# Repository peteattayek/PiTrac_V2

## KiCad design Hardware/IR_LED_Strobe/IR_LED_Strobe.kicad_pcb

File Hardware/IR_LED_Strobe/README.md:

# IR LED strobe array

This two-layer emitter board connects to J3 on the [controller](../The_One_Board_To_Rule_Them_All/README.md).
The controller contains the driver; this board carries the LEDs and their series resistors.
Open [IR_LED_Strobe.kicad_pro](IR_LED_Strobe.kicad_pro) to edit it, or read the
[two-sheet schematic PDF](exports/IR_LED_Strobe.pdf). See the [wiring guide, section 5](../../WIRING_DIAGRAM.md#5-irled--irled2-strobe-board-wiring-j3)
for the connector pinout. `VIR-` is the switched return, not ground.

## Current assembly

The PCB has four parallel strings of five LED positions. **Only the two middle rows
are fitted: 10 LEDs, not 20** (owner-confirmed 2026-11-20). The schematic and layout
show the full design, not just the fitted parts.

| Row in PCB editor (top to bottom) | LED references | Current assembly |
|---|---|---|
| 1 | D1–D5 | Empty |
| 2 | D6–D10 | Fitted |
| 3 | D11–D15 | Fitted |
| 4 | D16–D20 | Empty |

## Files

- [PCB layout](IR_LED_Strobe.kicad_pcb) and [root schematic](IR_LED_Strobe.kicad_sch).
  The only child sheet is [IRLED.kicad_sch](IRLED.kicad_sch).
- [VSMA1085250.pretty](VSMA1085250.pretty/) contains the LED footprint recovered from
  the original PCB. The library name matches the layout; the LED specified in the
  schematic is `VSMA1085400x02`.
- [exports/](exports/) contains the schematic PDF and the original [mechanical STEP](exports/IR_LED_Strobe.step).
- [jlcpcb/production_files/](jlcpcb/production_files/) contains the original Gerber ZIP,
  assembly BOM and placement list. Their historical filenames are intentional.
  The BOM and placement list contain R1–R4 only; neither is a list of the fitted LEDs.

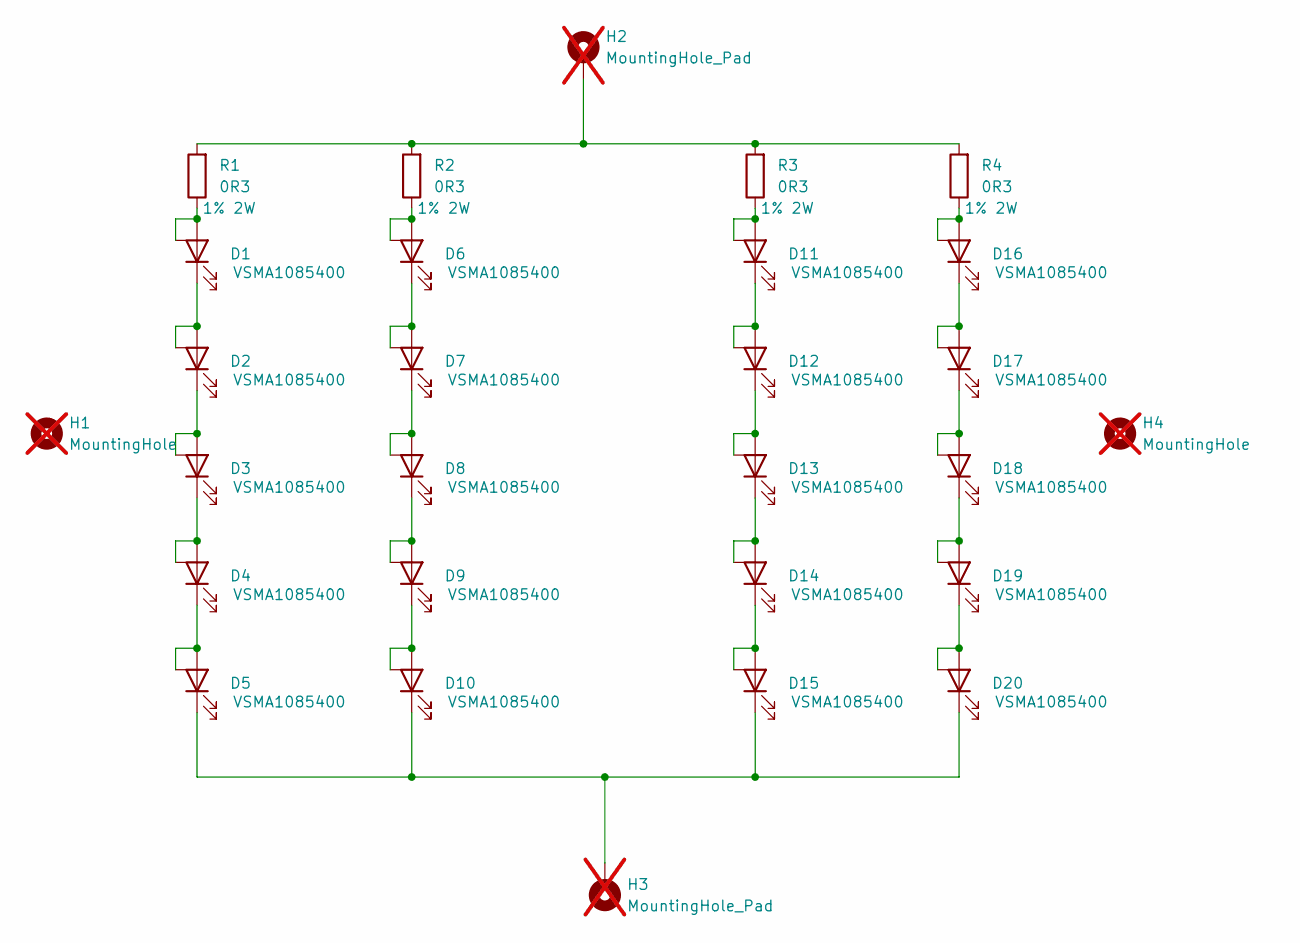
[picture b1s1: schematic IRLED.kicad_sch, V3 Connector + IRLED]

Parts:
D1, D2, D3, D4, D5, D6, D7, D8, D9, D10, D11, D12, D13, D14, D15, D16, D17, D18, D19, D20: VSMA1085400x02; DIODE_VSMA1085250_VIS; Part Number VSMA1085400
H1, H4: MountingHole; MountingHole_3.2mm_M3; not fitted
H2, H3: MountingHole_Pad; MountingHole_2.2mm_M2_Pad; not fitted
R1, R2, R3, R4: 0R3; R_2512_6332Metric; Ratings 1% 2W; Part Number KNP100JR-73-0R1; LCSC C149850

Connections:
unnamed: D1.2 (A), D1.3, R1.1
unnamed: D1.1 (K), D2.2 (A), D2.3
unnamed: D2.1 (K), D3.2 (A), D3.3
unnamed: D3.1 (K), D4.2 (A), D4.3
unnamed: D4.1 (K), D5.2 (A), D5.3
unnamed: D6.2 (A), D6.3, R2.1
unnamed: D6.1 (K), D7.2 (A), D7.3
unnamed: D7.1 (K), D8.2 (A), D8.3
unnamed: D8.1 (K), D9.2 (A), D9.3
unnamed: D9.1 (K), D10.2 (A), D10.3
unnamed 10: D5.1 (K), D10.1 (K), D15.1 (K), D20.1 (K), H3.1; also elsewhere on the board
unnamed: D11.2 (A), D11.3, R3.1
unnamed: D11.1 (K), D12.2 (A), D12.3
unnamed: D12.1 (K), D13.2 (A), D13.3
unnamed: D13.1 (K), D14.2 (A), D14.3
unnamed: D14.1 (K), D15.2 (A), D15.3
unnamed: D16.2 (A), D16.3, R4.1
unnamed: D16.1 (K), D17.2 (A), D17.3
unnamed: D17.1 (K), D18.2 (A), D18.3
unnamed: D18.1 (K), D19.2 (A), D19.3
unnamed: D19.1 (K), D20.2 (A), D20.3
unnamed 21: H2.1, R1.2, R2.2, R3.2, R4.2; also elsewhere on the board

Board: 2 copper layers, 28 parts (0 on the bottom side), 22 nets, no tracks yet.

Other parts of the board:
VIR+: MountingHole_Pad; MountingHole_2.2mm_M2_Pad
VIR-: MountingHole_Pad; MountingHole_2.2mm_M2_Pad

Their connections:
unnamed 10: VIR-.1 (1_1); also elsewhere on the board
unnamed 21: VIR+.1 (1_1); also elsewhere on the board

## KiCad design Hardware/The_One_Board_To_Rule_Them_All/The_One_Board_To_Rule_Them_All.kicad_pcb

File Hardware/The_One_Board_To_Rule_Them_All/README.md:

# The one board to rule them all

This is the Rev V1 controller for the PiTrac V2 golf launch monitor. It detects the
ball crossing the infrared beam, times the cameras and strobe, and interfaces with
the Raspberry Pi. **To edit the board, open the [KiCad 10 project](The_One_Board_To_Rule_Them_All.kicad_pro).**
To read the circuit without KiCad, open the [schematic PDF](exports/The_One_Board_To_Rule_Them_All.pdf).
The [external IR LED array](../IR_LED_Strobe/README.md) driven by J3 has its own PCB project.

| Where | What's in it |
|---|---|
| Project root | The editable four-layer [PCB](The_One_Board_To_Rule_Them_All.kicad_pcb), design rules (`.kicad_dru`), [root schematic](The_One_Board_To_Rule_Them_All.kicad_sch) and seven child sheets. |
| Libraries at the root | Two symbol libraries (`.kicad_sym`), two footprint libraries (`.pretty/`) and `fp-lib-table`. Keep these beside the project. |
| [exports/](exports/) | [Netlist](exports/The_One_Board_To_Rule_Them_All.net) used by the firmware hardware-reference report, schematic PDF, parts list (BOM), and 22 SVG layer plots in plain and color versions. These are outputs, not the editable design. |
| [jlcpcb/](jlcpcb/) | Manufacturing record: copper, mask, paste, silkscreen, outline and drill files; plugin database; and the [production package](jlcpcb/production_files/) with the Gerber ZIP, assembly BOM and placement list. Its original filenames and contents are preserved as sent to the fab. |
| [legacy/](legacy/) | Two unused schematics (`IRLED` and the empty `MCU` sheet) and a second text netlist that differs only in its export timestamp. The original project ZIP, if present, is a local backup not tracked by Git. |

### Which schematic should I edit?

| Circuit | Active sheet |
|---|---|
| Power input, rails and switching | [Power.kicad_sch](Power.kicad_sch) |
| MCU, USB, Pi and camera connectors | [RP2350_80QFN_minimal.kicad_sch](RP2350_80QFN_minimal.kicad_sch) |
| Beam LED driver (not the camera strobe) | [strobe.kicad_sch](strobe.kicad_sch) |
| Camera strobe driver | [Strobe Generation.kicad_sch](Strobe%20Generation.kicad_sch) |
| Photodiode amplifier | [photodiode.kicad_sch](photodiode.kicad_sch) |
| Photodiode demodulator and comparator | [photodiode_demodulation.kicad_sch](photodiode_demodulation.kicad_sch) |
| Impact microphone | [microphone.kicad_sch](microphone.kicad_sch) |

The rename is not a new hardware revision. Historical exports and manufacturing
files can still say “The Second Board To Rule Them All.” For the circuit's theory
of operation, see the [original design document](../The_One_Board_To_Rule_Them_All.md).

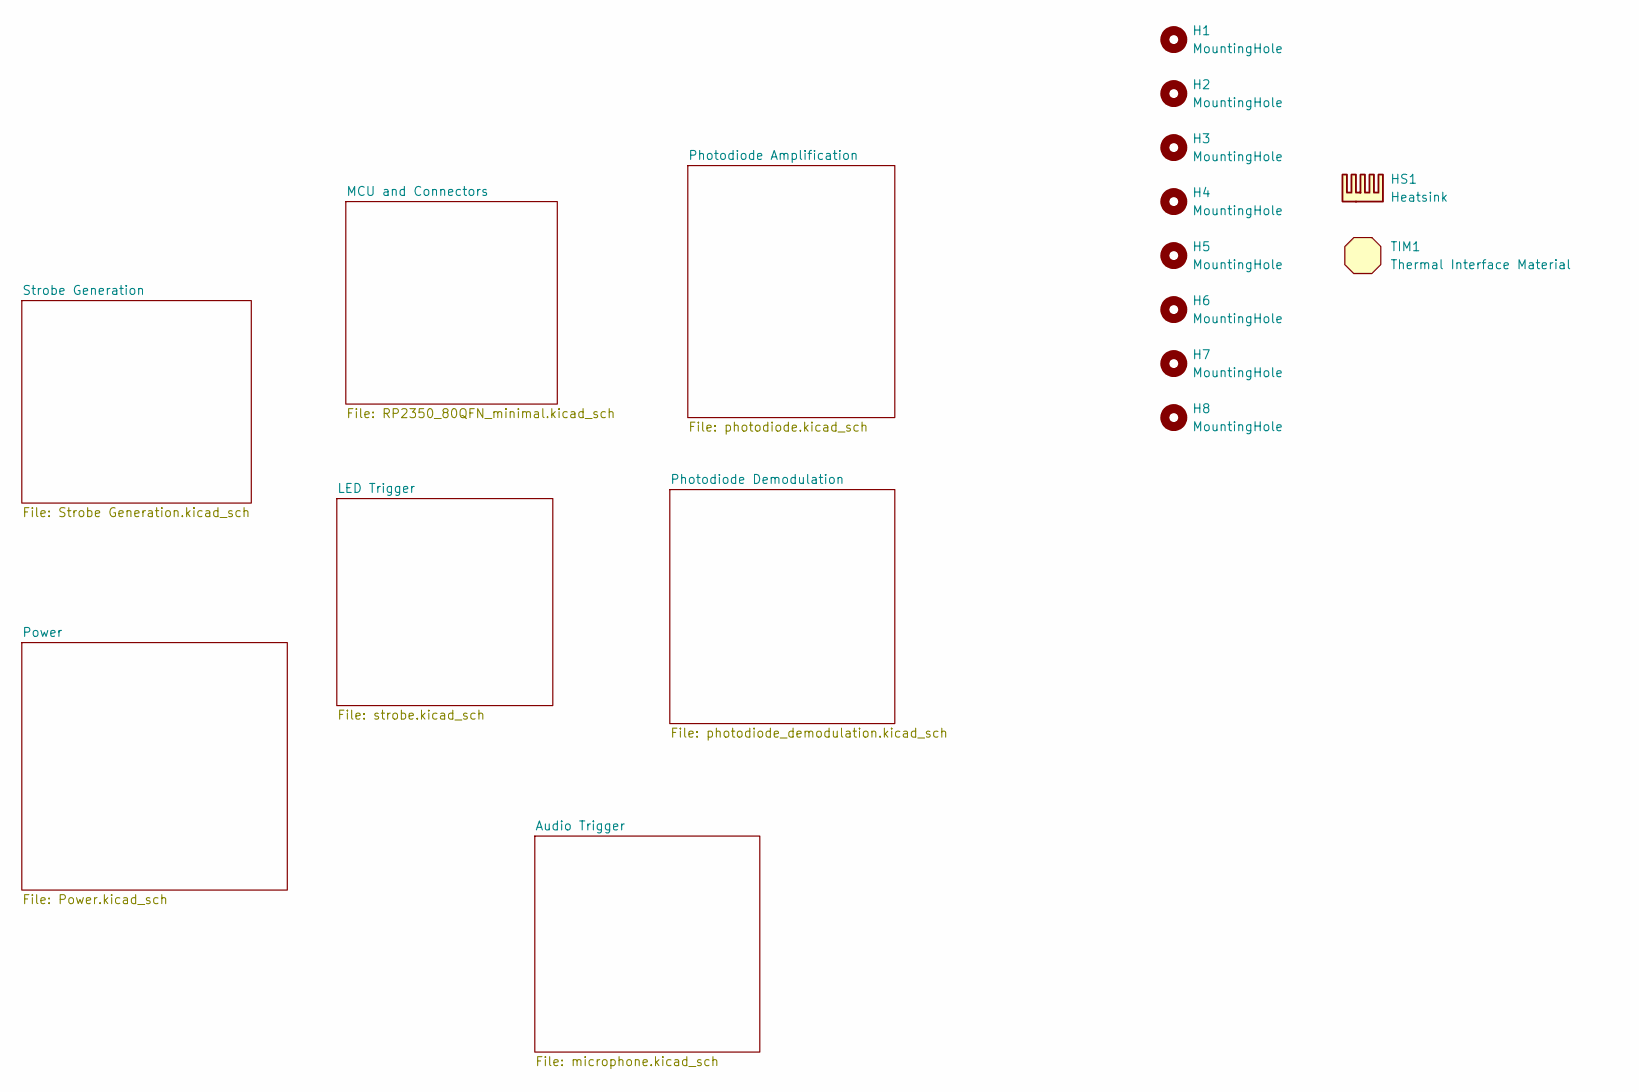
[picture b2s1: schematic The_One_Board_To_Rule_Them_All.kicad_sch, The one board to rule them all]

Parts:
H1, H2, H7, H8: MountingHole; MountingHole_2.2mm_M2
H3, H4, H5, H6: MountingHole; MountingHole_2.7mm_M2.5
HS1: Heatsink; Ratings <= 27 C/W; MPN HSB09-212115
TIM1: Thermal Interface Material; MPN TG-T1000-20-20-0.25-5PT

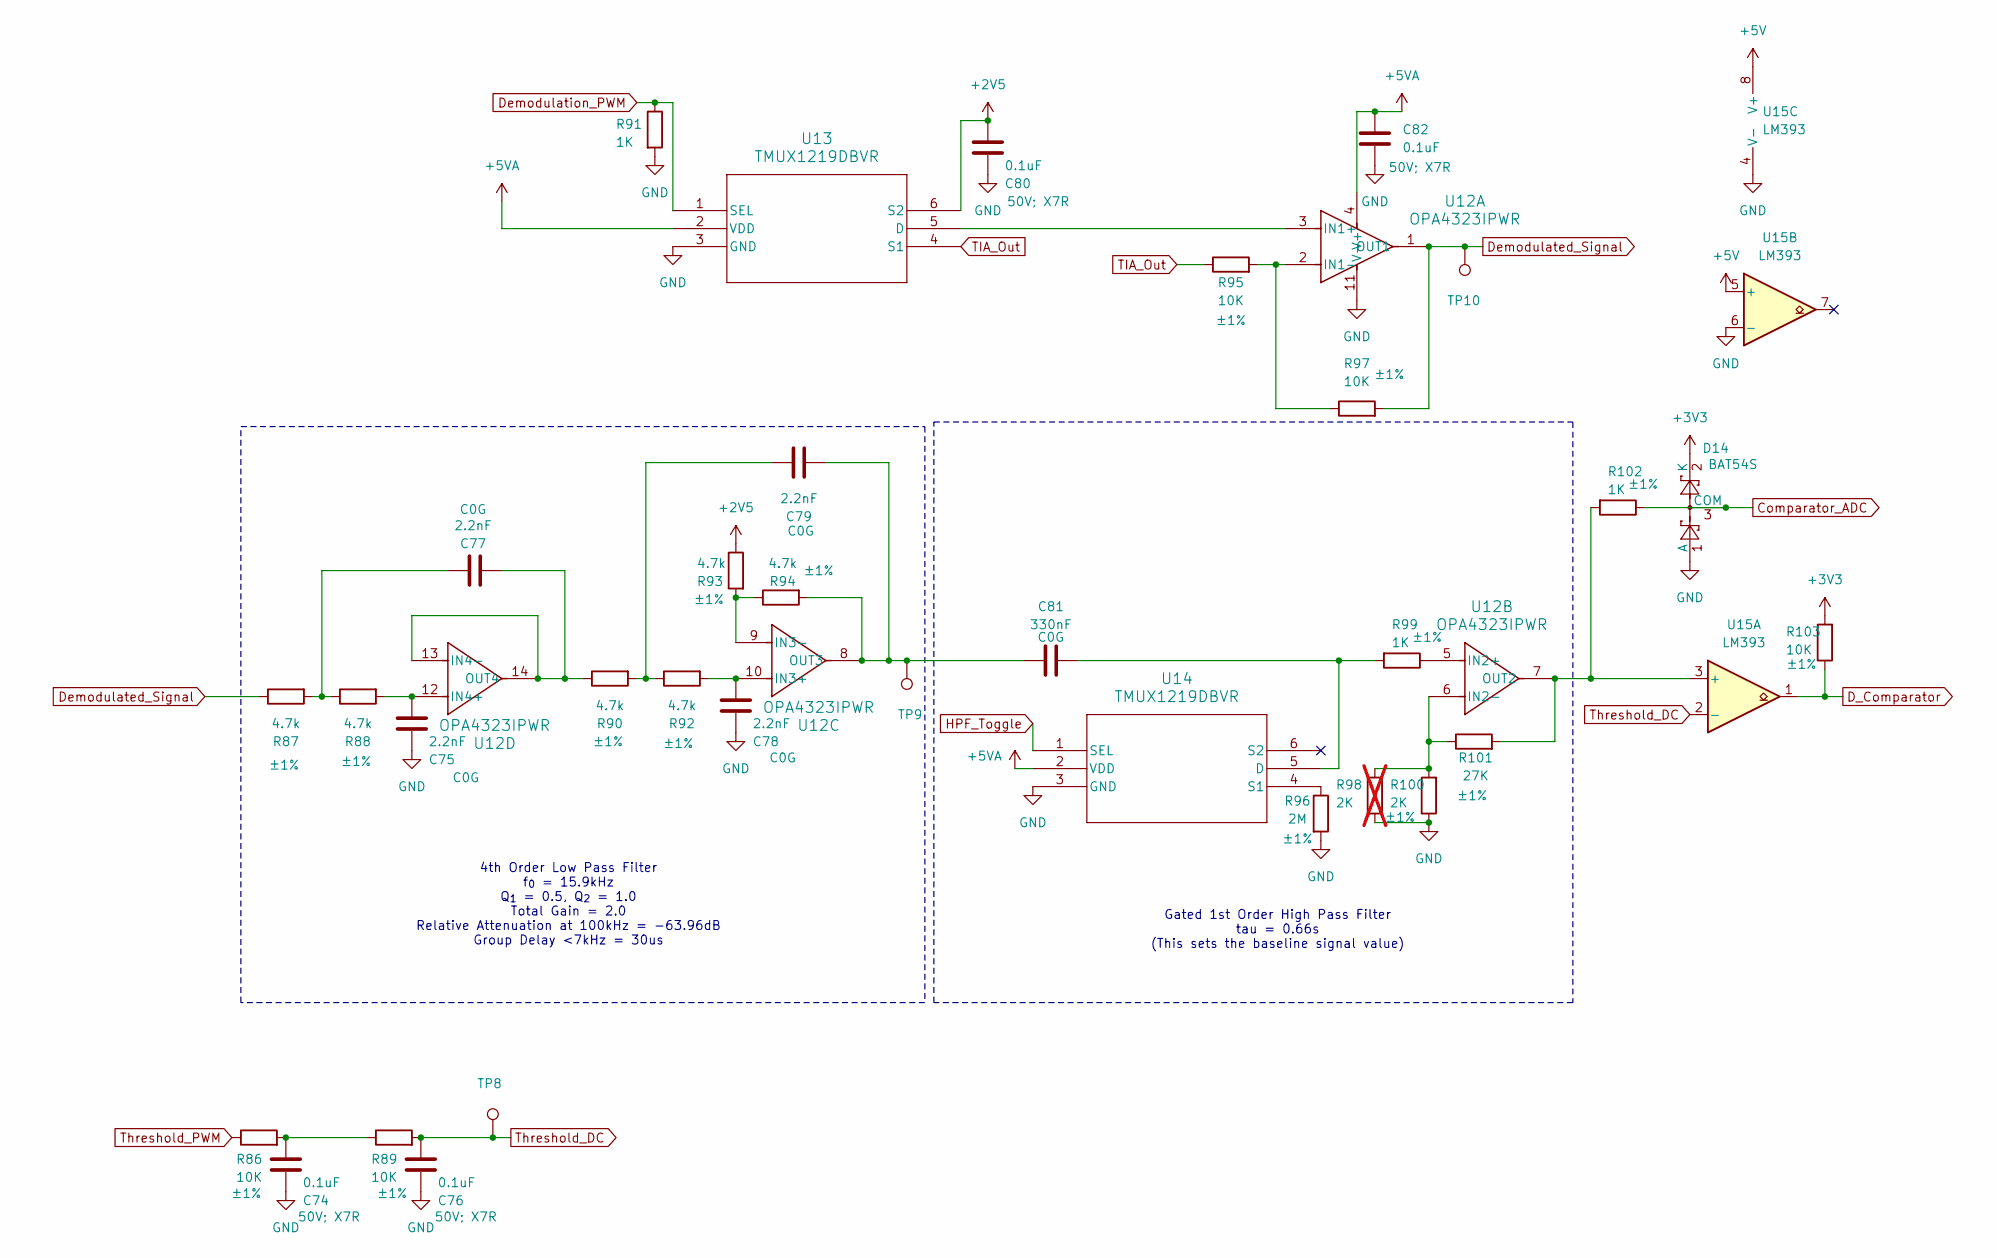
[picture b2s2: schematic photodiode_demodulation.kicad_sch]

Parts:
C74, C76, C80, C82: 0.1uF; C_0402_1005Metric; Ratings 50V; X7R; MPN CL05B104KB54PNC; LCSC C307331
C75, C77, C78, C79: 2.2nF; C_0805_2012Metric; Ratings C0G; MPN CL21C222JBFNNNE; LCSC C28260
C81: 330nF; C_1206_3216Metric; Ratings C0G; MPN GRM31C5C1E334JE01L; LCSC C3837965
D14: BAT54S; SOT-23; MPN BAT54SLT1G; LCSC C7420333
R86, R89, R95, R97, R103: 10K; R_0402_1005Metric; Ratings ±1%; MPN RMCF0402FT10K0; LCSC C25744
R87, R88, R90, R92, R93, R94: 4.7k; R_0402_1005Metric; Ratings ±1%; MPN RMCF0402FT4K70; LCSC C25900
R91, R99, R102: 1K; R_0402_1005Metric; Ratings ±1%; MPN RMCF0402FT1K00; LCSC C11702
R96: 2M; R_0603_1608Metric; Ratings ±1%; MPN RMCF0603FT2M00; LCSC C22976
R98: 2K; R_0805_2012Metric_Pad1.20x1.40mm_HandSolder; Ratings ±1%; MPN RMCF0805FT2K00; not fitted
R100: 2K; R_0805_2012Metric_Pad1.20x1.40mm_HandSolder; Ratings ±1%; MPN RMCF0805FT2K00; LCSC C17604
R101: 27K; R_0402_1005Metric; Ratings ±1%; MPN RMCF0402FT27K0; LCSC C25771
TP8, TP9, TP10: TestPoint; TestPoint_THTPad_D1.0mm_Drill0.5mm
U12: OPA4323IPWR; PW0014A-IPC_A; MPN OPA4323IPWR; LCSC C22419728
U13, U14: TMUX1219DBVR; SOT-23-6_DBV_TEX; MPN TMUX1219DBVR; LCSC C2869838
U15: LM393; SOIC-8_3.9x4.9mm_P1.27mm; MPN LM393DR2G; Digikey PN LM393DR2GOSCT-ND

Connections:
+2V5: C80.2, R93.1, U13.6 (S2); also elsewhere on the board
+3V3: D14.2 (K), R103.2; also elsewhere on the board
+5V: U15.5 (+), U15.8 (V+); also elsewhere on the board
+5VA: C82.1, U12.4 (V+), U13.2 (VDD), U14.2 (VDD); also elsewhere on the board
Comparator_ADC: D14.3 (COM), R102.1; also elsewhere on the board
D_Comparator: R103.1, U15.1; also elsewhere on the board
Demodulated_Signal: R87.1, R97.2, TP10.1 (1_1), U12.1 (OUT1)
Demodulation_PWM: R91.1, U13.1 (SEL); also elsewhere on the board
GND: C74.1, C75.1, C76.1, C78.1, C80.1, C82.2, D14.1 (A), R91.2, R96.2, R98.1, R100.1, U12.11 (V-), U13.3 (GND), U14.3 (GND), U15.4 (V-), U15.6 (-); also elsewhere on the board
HPF_Toggle: U14.1 (SEL); also elsewhere on the board
unnamed: C74.2, R86.2, R89.1
unnamed: C77.1, R87.2, R88.1
unnamed: C79.1, R90.2, R92.1
unnamed: U12.3 (IN1+), U13.5 (D)
unnamed: R95.2, R97.1, U12.2 (IN1-)
unnamed: R99.1, U12.5 (IN2+)
unnamed: R98.2, R100.2, R101.1, U12.6 (IN2-)
unnamed: R101.2, R102.2, U12.7 (OUT2), U15.3 (+)
unnamed: C78.2, R92.2, U12.10 (IN3+)
unnamed: R93.2, R94.1, U12.9 (IN3-)
unnamed: C79.2, C81.1, R94.2, TP9.1 (1_1), U12.8 (OUT3)
unnamed: C75.2, R88.2, U12.12 (IN4+)
unnamed: C77.2, R90.1, U12.13 (IN4-), U12.14 (OUT4)
unnamed: C81.2, R99.2, U14.5 (D)
unnamed: R96.1, U14.4 (S1)
TIA_Out: R95.1, U13.4 (S1); also elsewhere on the board
Threshold_DC: C76.2, R89.2, TP8.1 (1_1), U15.2 (-)
Threshold_PWM: R86.1; also elsewhere on the board

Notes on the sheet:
Gated 1st Order High Pass Filter tau = 0.66s (This sets the baseline signal value)
4th Order Low Pass Filter f_{0} = 15.9kHz Q_{1} = 0.5, Q_{2} = 1.0 Total Gain = 2.0 Relative Attenuation at 100kHz = -63.96dB Group Delay <7kHz = 30us

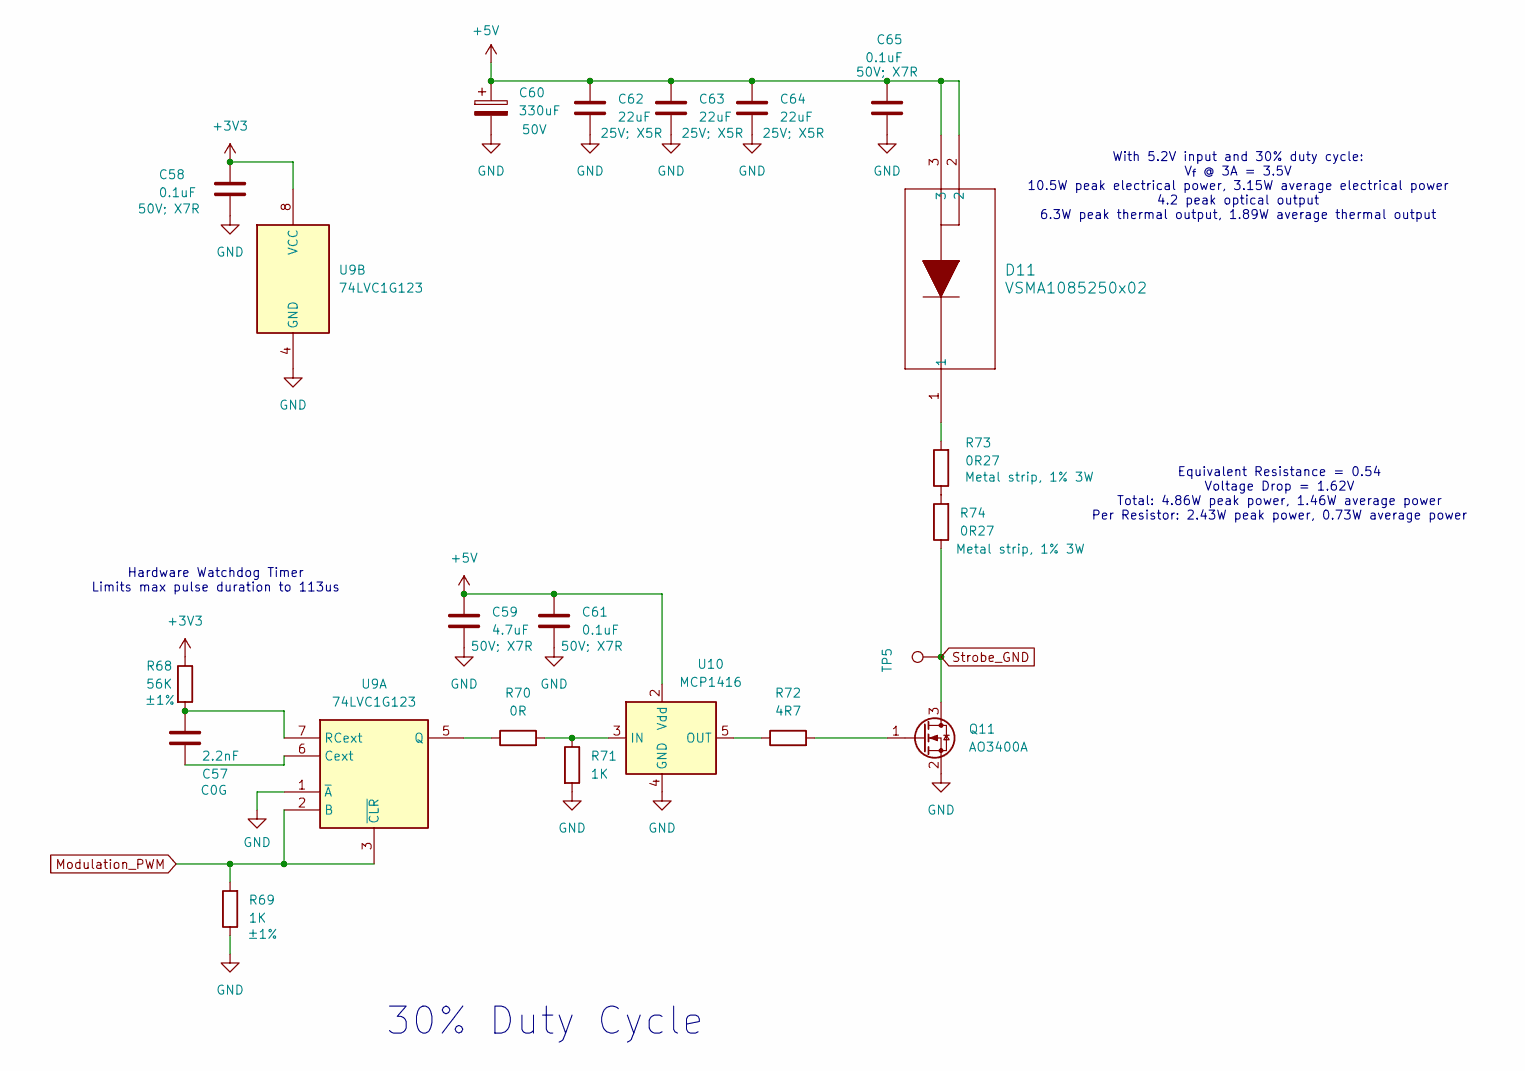
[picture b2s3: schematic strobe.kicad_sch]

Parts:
C57: 2.2nF; C_0805_2012Metric; Ratings C0G; MPN CL21C222JBFNNNE; LCSC C28260
C58, C61, C65: 0.1uF; C_0402_1005Metric; Ratings 50V; X7R; MPN CL05B104KB54PNC; LCSC C307331
C59: 4.7uF; C_1206_3216Metric; Ratings 50V; X7R; MPN CL31B475KBHNFNE; LCSC C29823
C60: 330uF; CAP_50TPV_10x10.5_RBY; Ratings 50V; MPN 50TPV330M10X10.5; LCSC C53120968
C62, C63, C64: 22uF; C_1206_3216Metric; Ratings 25V; X5R; MPN CL31A226KAHNNNE; LCSC C12891
D11: VSMA1085250x02; DIODE_VSMA1085250_VIS; MPN VSMA1085250X02; LCSC C20346087
Q11: AO3400A; SOT-23; MPN AO3400A; Digikey PN 785-1000-1-ND
R68: 56K; R_0603_1608Metric; Ratings ±1%; MPN RMCF0603FT56K0; LCSC C23206
R69, R71: 1K; R_0402_1005Metric; Ratings ±1%; MPN RMCF0402FT1K00; LCSC C11702
R70: 0R; R_0805_2012Metric_Pad1.20x1.40mm_HandSolder; MPN RMCF0805ZT0R00; LCSC C17477
R72: 4R7; R_0805_2012Metric; Ratings ±1%; MPN RMCF0805FT4R70; LCSC C17675
R73, R74: 0R27; R_2512_6332Metric; Ratings Metal strip, 1% 3W; MPN HoJLR2512-3W-270mR-1%; LCSC C2903472
TP5: TestPoint; TestPoint_THTPad_D1.0mm_Drill0.5mm
U9: 74LVC1G123; VSSOP-8_2.3x2mm_P0.5mm; MPN SN74LVC1G123DCUR; LCSC C26159250
U10: MCP1416; SOT-23-5; MPN MCP1416T-E/OT; LCSC C83775

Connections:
+3V3: C58.1, R68.1, U9.8 (VCC); also elsewhere on the board
+5V: C59.1, C60.1, C61.1, C62.1, C63.1, C64.1, C65.2, D11.2, D11.3, U10.2 (Vdd); also elsewhere on the board
GND: C58.2, C59.2, C60.2, C61.2, C62.2, C63.2, C64.2, C65.1, Q11.2 (S), R69.1, R71.2, U9.1 (~A), U9.4 (GND), U10.4 (GND); also elsewhere on the board
Modulation_PWM: R69.2, U9.2 (B), U9.3 (~CLR); also elsewhere on the board
unnamed: D11.1, R73.2
unnamed: Q11.1 (G), R72.2
unnamed: R73.1, R74.2
unnamed: C57.1, U9.6 (Cext)
unnamed: R70.1, U9.5 (Q)
unnamed: C57.2, R68.2, U9.7 (RCext)
unnamed: R70.2, R71.1, U10.3 (IN)
unnamed: R72.1, U10.5 (OUT)
Strobe_GND: Q11.3 (D), R74.1, TP5.1 (1_1)

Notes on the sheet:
Hardware Watchdog Timer Limits max pulse duration to 113us
30% Duty Cycle
With 5.2V input and 30% duty cycle: V_{f} @ 3A = 3.5V 10.5W peak electrical power, 3.15W average electrical power 4.2 peak optical output 6.3W peak thermal output, 1.89W average thermal output
Equivalent Resistance = 0.54 Voltage Drop = 1.62V Total: 4.86W peak power, 1.46W average power Per Resistor: 2.43W peak power, 0.73W average power

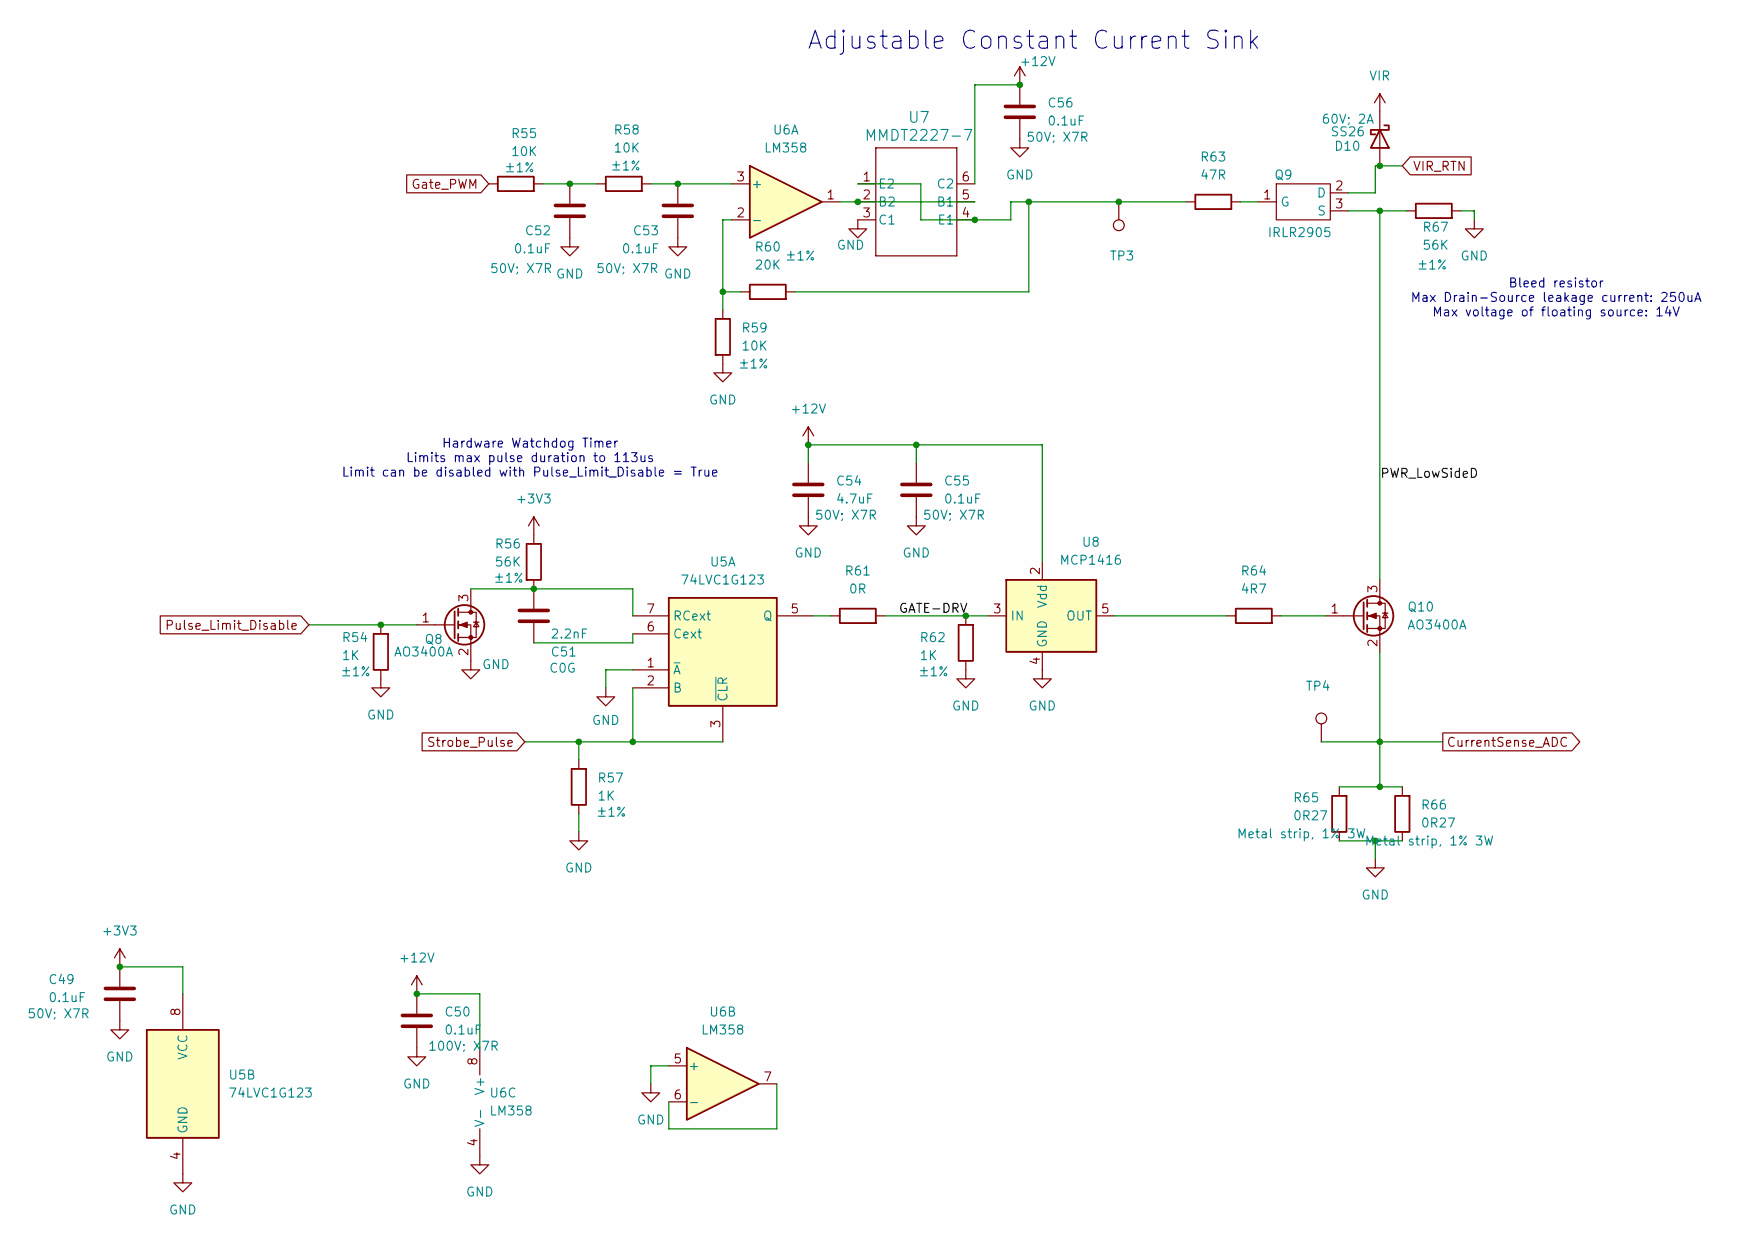
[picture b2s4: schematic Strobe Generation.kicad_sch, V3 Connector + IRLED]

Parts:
C49, C52, C53, C55, C56: 0.1uF; C_0402_1005Metric; Ratings 50V; X7R; MPN CL05B104KB54PNC; LCSC C307331
C50: 0.1uF; C_0805_2012Metric; Ratings 100V; X7R; MPN CL21B104KCFNNNE; LCSC C28233
C51: 2.2nF; C_0805_2012Metric; Ratings C0G; MPN CL21C222JBFNNNE; LCSC C28260
C54: 4.7uF; C_1206_3216Metric; Ratings 50V; X7R; MPN CL31B475KBHNFNE; LCSC C29823
D10: SS26; D_SMA; Ratings 60V; 2A; MPN SS26S-E3/5AT; LCSC C7420363
Q8, Q10: AO3400A; SOT-23; MPN AO3400A; Digikey PN 785-1000-1-ND
Q9: IRLR2905; ThermalVias; MPN IRLR2905TRPBF; LCSC C3010
R54, R57, R62: 1K; R_0402_1005Metric; Ratings ±1%; MPN RMCF0402FT1K00; LCSC C11702
R55, R58, R59: 10K; R_0402_1005Metric; Ratings ±1%; MPN RMCF0402FT10K0; LCSC C25744
R56, R67: 56K; R_0603_1608Metric; Ratings ±1%; MPN RMCF0603FT56K0; LCSC C23206
R60: 20K; R_0402_1005Metric; Ratings ±1%; MPN RMCF0402FT20K0; LCSC C25765
R61: 0R; R_0805_2012Metric_Pad1.20x1.40mm_HandSolder; MPN RMCF0805ZT0R00; LCSC C17477
R63: 47R; R_0402_1005Metric; Ratings ±1%; MPN RMCF0402FT47R0; LCSC C25118
R64: 4R7; R_0805_2012Metric; Ratings ±1%; MPN RMCF0805FT4R70; LCSC C17675
R65, R66: 0R27; R_2512_6332Metric; Ratings Metal strip, 1% 3W; MPN HoJLR2512-3W-270mR-1%; LCSC C2903472
TP3, TP4: TestPoint; TestPoint_THTPad_D1.0mm_Drill0.5mm
U5: 74LVC1G123; VSSOP-8_2.3x2mm_P0.5mm; MPN SN74LVC1G123DCUR; LCSC C26159250
U6: LM358; SOIC-8_3.9x4.9mm_P1.27mm; MPN LM358DR2G; LCSC C7950
U7: MMDT2227-7; SOT-363_DIO; MPN MMDT2227-7-F; LCSC C41375117
U8: MCP1416; SOT-23-5; MPN MCP1416T-E/OT; LCSC C83775

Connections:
+3V3: C49.1, R56.1, U5.8 (VCC); also elsewhere on the board
+12V: C50.1, C54.1, C55.1, C56.1, U6.8 (V+), U7.6 (C2), U8.2 (Vdd); also elsewhere on the board
/Strobe Generation/GATE-DRV: R61.2, R62.2, U8.3 (IN)
/Strobe Generation/PWR_LowSideD: Q9.3 (S), Q10.3 (D), R67.1
CurrentSense_ADC: Q10.2 (S), R65.2, R66.2, TP4.1 (1_1); also elsewhere on the board
GND: C49.2, C50.2, C52.1, C53.1, C54.2, C55.2, C56.2, Q8.2 (S), R54.1, R57.1, R59.2, R62.1, R65.1, R66.1, R67.2, U5.1 (~A), U5.4 (GND), U6.4 (V-), U6.5 (+), U7.3 (C1), U8.4 (GND); also elsewhere on the board
Gate_PWM: R55.1; also elsewhere on the board
unnamed: C52.2, R55.2, R58.1
unnamed: C51.2, Q8.3 (D), R56.2, U5.7 (RCext)
unnamed: Q9.1 (G), R63.2
unnamed: Q10.1 (G), R64.2
unnamed: C51.1, U5.6 (Cext)
unnamed: R61.1, U5.5 (Q)
unnamed: C53.2, R58.2, U6.3 (+)
unnamed: R59.1, R60.1, U6.2 (-)
unnamed: U6.6 (-), U6.7
unnamed: U6.1, U7.2 (B2), U7.5 (B1)
unnamed: R60.2, R63.1, TP3.1 (1_1), U7.1 (E2), U7.4 (E1)
unnamed: R64.1, U8.5 (OUT)
Pulse_Limit_Disable: Q8.1 (G), R54.2; also elsewhere on the board
Strobe_Pulse: R57.2, U5.2 (B), U5.3 (~CLR); also elsewhere on the board
VIR: D10.1 (K); also elsewhere on the board
VIR_RTN: D10.2 (A), Q9.2 (D); also elsewhere on the board

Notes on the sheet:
Hardware Watchdog Timer Limits max pulse duration to 113us Limit can be disabled with Pulse_Limit_Disable = True
Adjustable Constant Current Sink
Bleed resistor Max Drain-Source leakage current: 250uA Max voltage of floating source: 14V

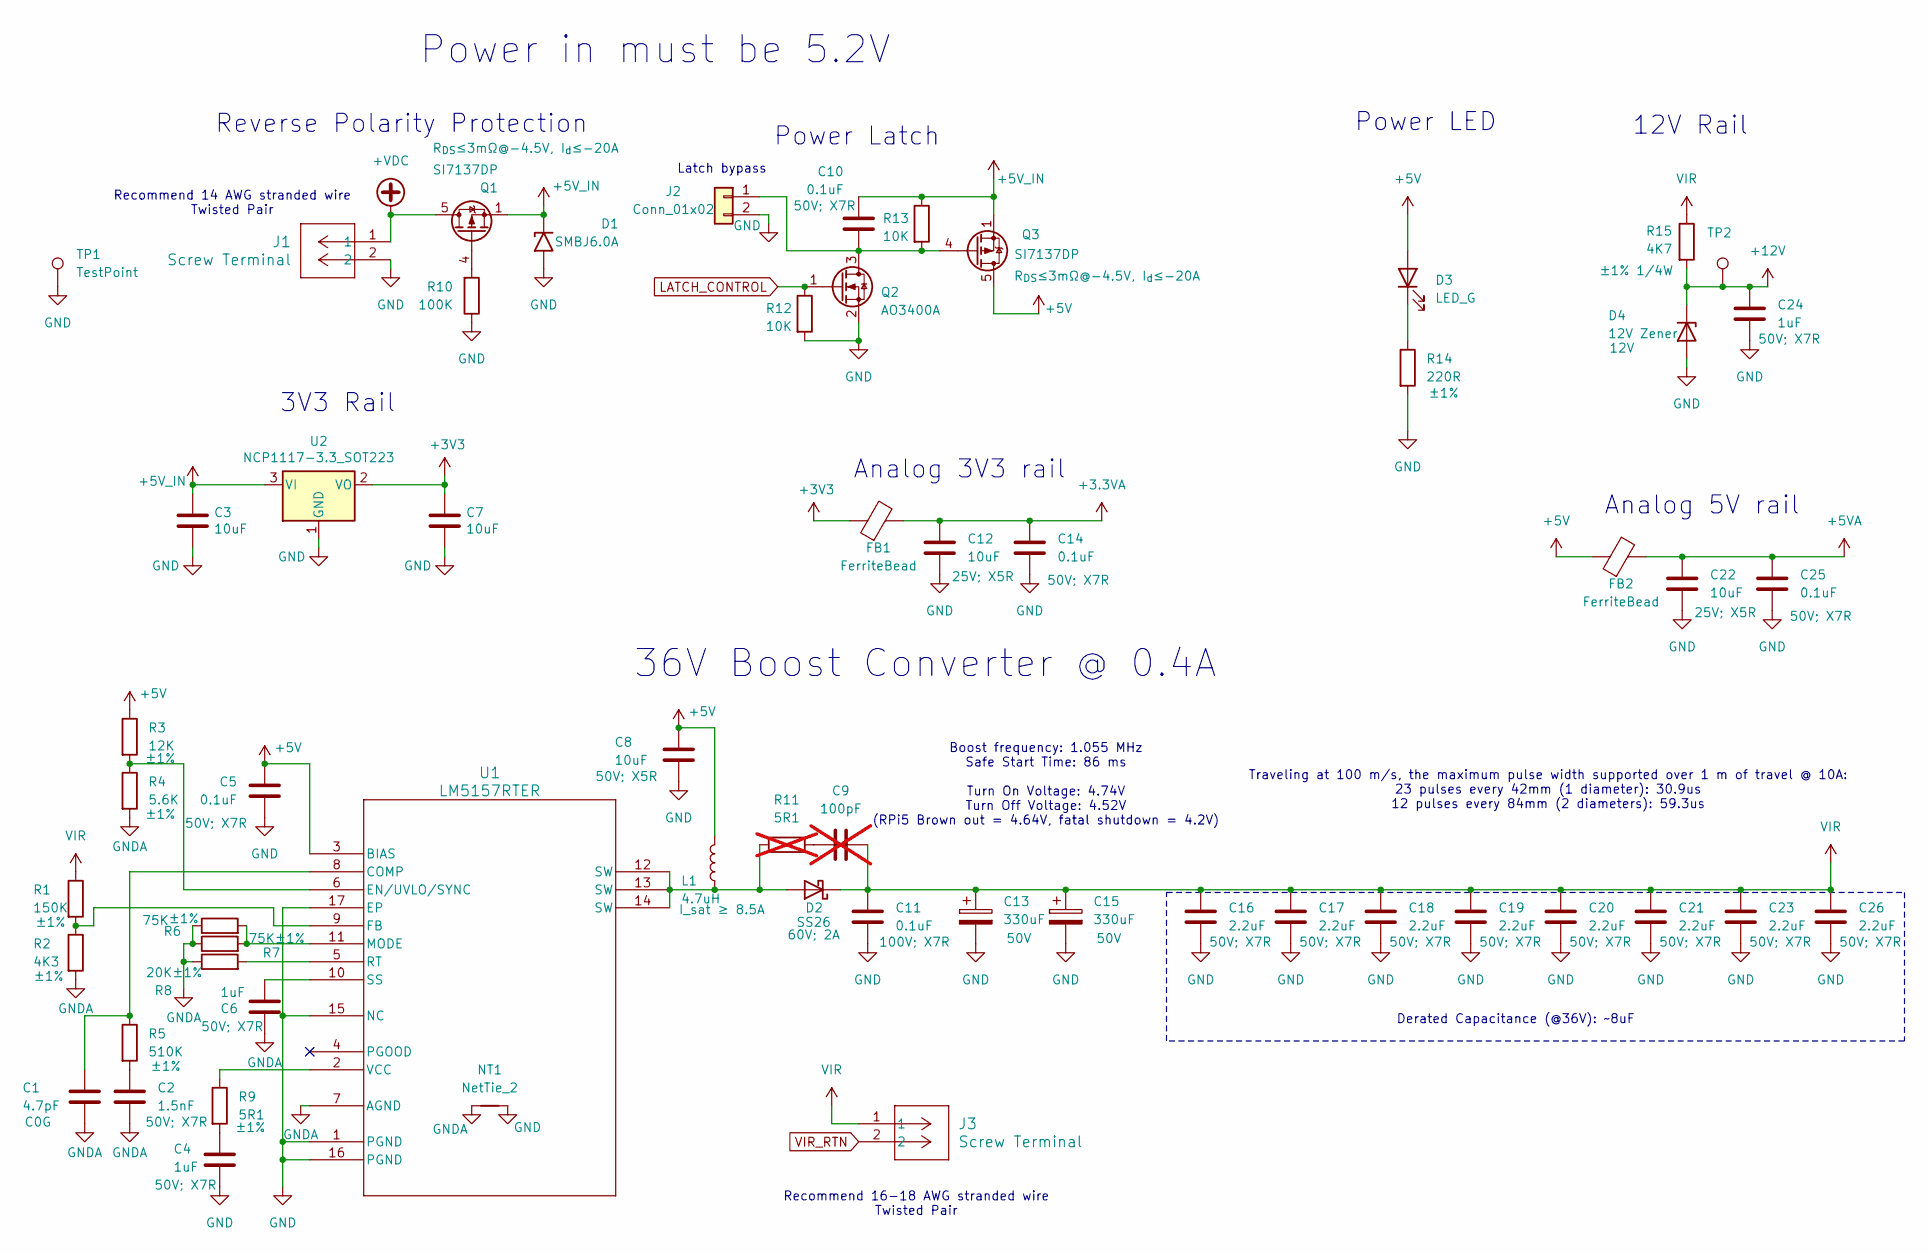
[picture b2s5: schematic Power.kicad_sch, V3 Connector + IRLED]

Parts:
C1: 4.7pF; C_0402_1005Metric; Ratings C0G; MPN GRM1555C1H4R7CA01D; LCSC C1569
C2: 1.5nF; C_0603_1608Metric; Ratings 50V; X7R; MPN GCD188R71H152KA01D; LCSC C1595
C3, C7, C12, C22: 10uF; C_0603_1608Metric; Ratings 25V; X5R; MPN CL10A106MA8NRNC; LCSC C96446
C4, C6, C24: 1uF; C_0805_2012Metric; Ratings 50V; X7R; MPN CL21B105KBFNNNE; LCSC C28323
C5, C10, C14, C25: 0.1uF; C_0402_1005Metric; Ratings 50V; X7R; MPN CL05B104KB54PNC; LCSC C307331
C8: 10uF; C_0805_2012Metric; Ratings 50V; X5R; MPN GRM21BR61H106KE43L; LCSC C440198
C9: 100pF; C_0603_1608Metric; Ratings 100V, C0G; MPN GCM1885C2A101JA16D; not fitted
C11: 0.1uF; C_0805_2012Metric; Ratings 100V; X7R; MPN CL21B104KCFNNNE; LCSC C28233
C13, C15: 330uF; CAP_50TPV_10x10.5_RBY; Ratings 50V; MPN 50TPV330M10X10.5; LCSC C53120968
C16, C17, C18, C19, C20, C21, C23, C26: 2.2uF; C_1206_3216Metric; Ratings 50V; X7R; MPN CL31B225KBHNNNE; LCSC C50254
D1: SMBJ6.0A; D_SMB; MPN SMBJ6.0A; LCSC C19077560
D2: SS26; D_SMA; Ratings 60V; 2A; MPN SS26S-E3/5AT; LCSC C7420363
D3: LED_G; LED_0805_2012Metric; MPN APT2012LZGCK; LCSC C2297
D4: 12V Zener; D_SOD-123; Ratings 12V; MPN BZT52B12; LCSC C22395569
FB1, FB2: FerriteBead; L_0603_1608Metric; MPN BLM18PG121SN1D; LCSC C14709
J1, J3: Screw Terminal; CONN2_710002_WRE; MPN 691137710002
J2: Conn_01x02; PinHeader_1x02_P2.54mm_Vertical; MPN PH1-02-UA
L1: 4.7uH; L_Abracon_ASPI-0630LR; Ratings I_sat ≥ 8.5A; MPN ASPI-0630HI-4R7M-T15; LCSC C207840
NT1: NetTie_2; NetTie-2_SMD_Pad0.5mm
Q1, Q3: SI7137DP; PQFN-8-EP_6x5mm_P1.27mm_Generic_ThermalVias; Ratings R_{DS}≤3mΩ@-4.5V, I_{d}≤-20A; MPN SI7137DP-T1-GE3; LCSC C42456927
Q2: AO3400A; SOT-23; MPN AO3400A; LCSC C20917
R1: 150K; R_0603_1608Metric; Ratings ±1%; MPN RMCF0603FT150K; LCSC C22807
R2: 4K3; R_0603_1608Metric; Ratings ±1%; MPN RMCF0603FT4K30; LCSC C23159
R3: 12K; R_0603_1608Metric; Ratings ±1%; MPN RMCF0603FT12K0; LCSC C22790
R4: 5.6K; R_0603_1608Metric; Ratings ±1%; MPN RMCF0603FT5K60; LCSC C23189
R5: 510K; R_0603_1608Metric; Ratings ±1%; MPN RMCF0603FT510K; LCSC C23192
R6, R7: 75K; R_0603_1608Metric; Ratings ±1%; MPN RMCF0603FT75K0; LCSC C23242
R8: 20K; R_0603_1608Metric; Ratings ±1%; MPN RMCF0603FT20K0; LCSC C4184
R9: 5R1; R_0805_2012Metric; Ratings ±1%; MPN RMCF0805FT5R10; LCSC C17724
R10: 100K; R_0402_1005Metric; Ratings ±1%; MPN RMCF0402FT100K; LCSC C25741
R11: 5R1; R_0805_2012Metric; Ratings ±1%, Pulse-Withstanding; MPN ERJ-P06J5R1V; not fitted
R12, R13: 10K; R_0402_1005Metric; Ratings ±1%; MPN RMCF0402FT10K0; LCSC C25744
R14: 220R; R_0402_1005Metric; Ratings ±1%; MPN RMCF0402FT220R; LCSC C25091
R15: 4K7; R_1206_3216Metric; Ratings ±1% 1/4W; MPN RMCF1206FT4K70; LCSC C17936
TP1: TestPoint; TestPoint_Keystone_5000-5004_Miniature; MPN 5001; Digikey PN 36-5001-ND
TP2: TestPoint; TestPoint_THTPad_D1.0mm_Drill0.5mm
U1: LM5157RTER; QFN_57RTER_TEX_ThermalVias; MPN LM5157RTER; LCSC C5219222
U2: NCP1117-3.3_SOT223; SOT-223-3_TabPin2; MPN NCP1117ST33T3G; LCSC C6186

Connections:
+3.3VA: C12.2, C14.2, FB1.2; also elsewhere on the board
+3V3: C7.1, FB1.1, U2.2 (VO); also elsewhere on the board
+5V: C5.2, C8.1, D3.2 (A), FB2.1, L1.2, Q3.5 (D), R3.1, U1.3 (BIAS); also elsewhere on the board
+5VA: C22.2, C25.2, FB2.2; also elsewhere on the board
+5V_IN: C3.1, C10.2, D1.1 (A1), Q1.1 (S), Q1.2 (S), Q1.3 (S), Q3.1 (S), Q3.2 (S), Q3.3 (S), R13.1, U2.3 (VI); also elsewhere on the board
+12V: C24.1, D4.1 (K), R15.2, TP2.1 (1_1); also elsewhere on the board
+VDC: J1.1, Q1.5 (D)
GND: C3.2, C4.2, C5.1, C7.2, C8.2, C11.2, C12.1, C13.2, C14.1, C15.2, C16.2, C17.2, C18.2, C19.2, C20.2, C21.2, C22.1, C23.2, C24.2, C25.1, C26.2, D1.2 (A2), D4.2 (A), J1.2, J2.2, NT1.2, Q2.2 (S), R10.1, R12.2, R14.2, TP1.1 (1_1), U1.1 (PGND), U1.15 (NC), U1.16 (PGND), U1.17 (EP), U2.1 (GND); also elsewhere on the board
GNDA: C1.2, C2.2, C6.2, NT1.1, R2.2, R4.2, R6.1, R7.1, R8.1, U1.7 (AGND)
LATCH_CONTROL: Q2.1 (G), R12.1; also elsewhere on the board
unnamed: C2.1, R5.2
unnamed: C4.1, R9.2
unnamed: C9.1, R11.2
unnamed: D2.2 (A), L1.1, R11.1, U1.12 (SW), U1.13 (SW), U1.14 (SW)
unnamed: D3.1 (K), R14.1
unnamed: C10.1, J2.1, Q2.3 (D), Q3.4 (G), R13.2
unnamed: Q1.4 (G), R10.2
unnamed: C1.1, R5.1, U1.8 (COMP)
unnamed: R3.2, R4.1, U1.6 (EN/UVLO/SYNC)
unnamed: R1.2, R2.1, U1.9 (FB)
unnamed: R6.2, R7.2, U1.11 (MODE)
unnamed: R8.2, U1.5 (RT)
unnamed: C6.1, U1.10 (SS)
unnamed: R9.1, U1.2 (VCC)
VIR: C9.2, C11.1, C13.1, C15.1, C16.1, C17.1, C18.1, C19.1, C20.1, C21.1, C23.1, C26.1, D2.1 (K), J3.1, R1.1, R15.1; also elsewhere on the board
VIR_RTN: J3.2; also elsewhere on the board

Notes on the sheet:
Traveling at 100 m/s, the maximum pulse width supported over 1 m of travel @ 10A: 23 pulses every 42mm (1 diameter): 30.9us 12 pulses every 84mm (2 diameters): 59.3us
Power Latch
Recommend 16-18 AWG stranded wire Twisted Pair
Power in must be 5.2V
Derated Capacitance (@36V): ~8uF
Analog 5V rail
Reverse Polarity Protection
Recommend 14 AWG stranded wire Twisted Pair
36V Boost Converter @ 0.4A
Analog 3V3 rail
12V Rail
Power LED
Latch bypass
Boost frequency: 1.055 MHz Safe Start Time: 86 ms Turn On Voltage: 4.74V Turn Off Voltage: 4.52V (RPi5 Brown out = 4.64V, fatal shutdown = 4.2V)
3V3 Rail
